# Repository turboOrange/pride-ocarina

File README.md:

# pride-ocarina
An arduino nano based queer electronic ocarina
This was supposed to be used in a pride related workshop where I would spark curiosity with a little electronic soldering course.
The circuit do 2 things. First it has animated leds that shows queer flag colors with animation.
Second it's an electric ocarina based on the 6 holes kind.
It's engineered in a way that it's easy to understand and solder, not to be elegant.
The workshop hasn't been approved so I will keep this unfinished work for maybe a futur pride event.

Here is how it looks like at the moment:

## BOM
- 1 arduino nano
- 6 RGB lets
- 7 push buttons
- 1 9V battery with switch
- 2 double side sticker
- 1 100Ohm resistor
- 6 220Ohm resistor
- 1 motherboard internal speaker
- 1 custom bord
- 1 74HC138
- 1 10kOhm resistor

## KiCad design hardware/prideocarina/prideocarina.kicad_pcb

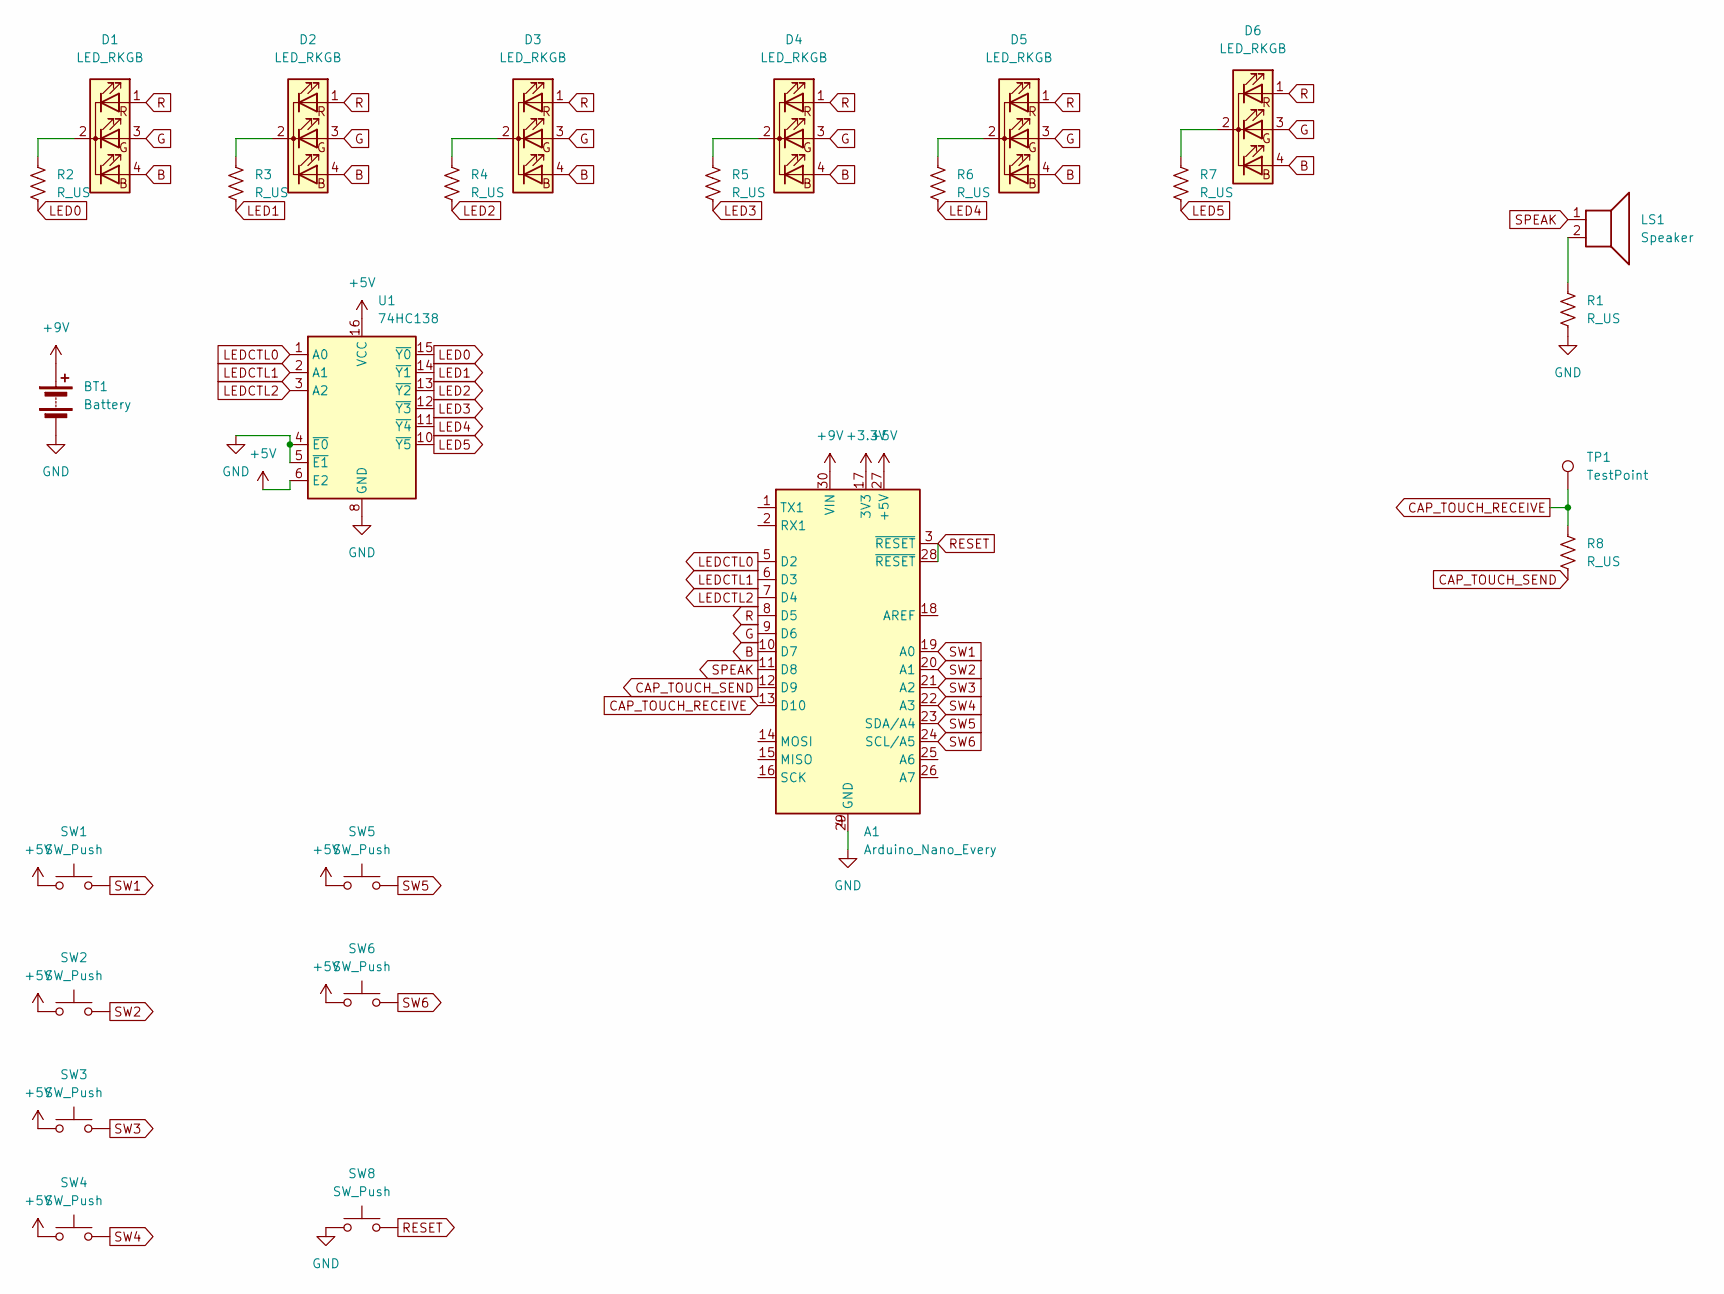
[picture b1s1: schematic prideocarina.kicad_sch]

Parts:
A1: Arduino_Nano_Every; Arduino_Nano
BT1: Battery
D1, D2, D3, D4, D5, D6: LED_RKGB; LED_D5.0mm-4_RGB
LS1: Speaker
R1, R2, R3, R4, R5, R6, R7, R8: R_US; R_Axial_DIN0309_L9.0mm_D3.2mm_P12.70mm_Horizontal
SW1, SW2, SW3, SW4, SW5, SW6, SW8: SW_Push
TP1: TestPoint; MountingHole_8.4mm_M8_Pad_Via
U1: 74HC138; DIP-16_W7.62mm

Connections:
+3.3V: A1.17 (3V3)
+5V: A1.27 (+5V), SW1.1, SW2.1, SW3.1, SW4.1, SW5.1, SW6.1, U1.6 (E2), U1.16 (VCC)
+9V: A1.30 (VIN), BT1.1 (+)
B: A1.10 (D7), D1.4 (BA), D2.4 (BA), D3.4 (BA), D4.4 (BA), D5.4 (BA), D6.4 (BA)
CAP_TOUCH_RECEIVE: A1.13 (D10), R8.1, TP1.1
CAP_TOUCH_SEND: A1.12 (D9), R8.2
G: A1.9 (D6), D1.3 (GA), D2.3 (GA), D3.3 (GA), D4.3 (GA), D5.3 (GA), D6.3 (GA)
GND: A1.4 (GND), A1.29 (GND), BT1.2 (-), R1.2, SW8.1, U1.4 (~E0), U1.5 (~E1), U1.8 (GND)
LED0: R2.2, U1.15 (~Y0)
LED1: R3.2, U1.14 (~Y1)
LED2: R4.2, U1.13 (~Y2)
LED3: R5.2, U1.12 (~Y3)
LED4: R6.2, U1.11 (~Y4)
LED5: R7.2, U1.10 (~Y5)
LEDCTL0: A1.5 (D2), U1.1 (A0)
LEDCTL1: A1.6 (D3), U1.2 (A1)
LEDCTL2: A1.7 (D4), U1.3 (A2)
unnamed: D1.2 (K), R2.1
unnamed: D2.2 (K), R3.1
unnamed: D3.2 (K), R4.1
unnamed: D4.2 (K), R5.1
unnamed: D5.2 (K), R6.1
unnamed: D6.2 (K), R7.1
unnamed: LS1.2, R1.1
R: A1.8 (D5), D1.1 (RA), D2.1 (RA), D3.1 (RA), D4.1 (RA), D5.1 (RA), D6.1 (RA)
RESET: A1.3 (~RESET), A1.28 (~RESET), SW8.2
SPEAK: A1.11 (D8), LS1.1
SW1: A1.19 (A0), SW1.2
SW2: A1.20 (A1), SW2.2
SW3: A1.21 (A2), SW3.2
SW4: A1.22 (A3), SW4.2
SW5: A1.23 (SDA/A4), SW5.2
SW6: A1.24 (SCL/A5), SW6.2

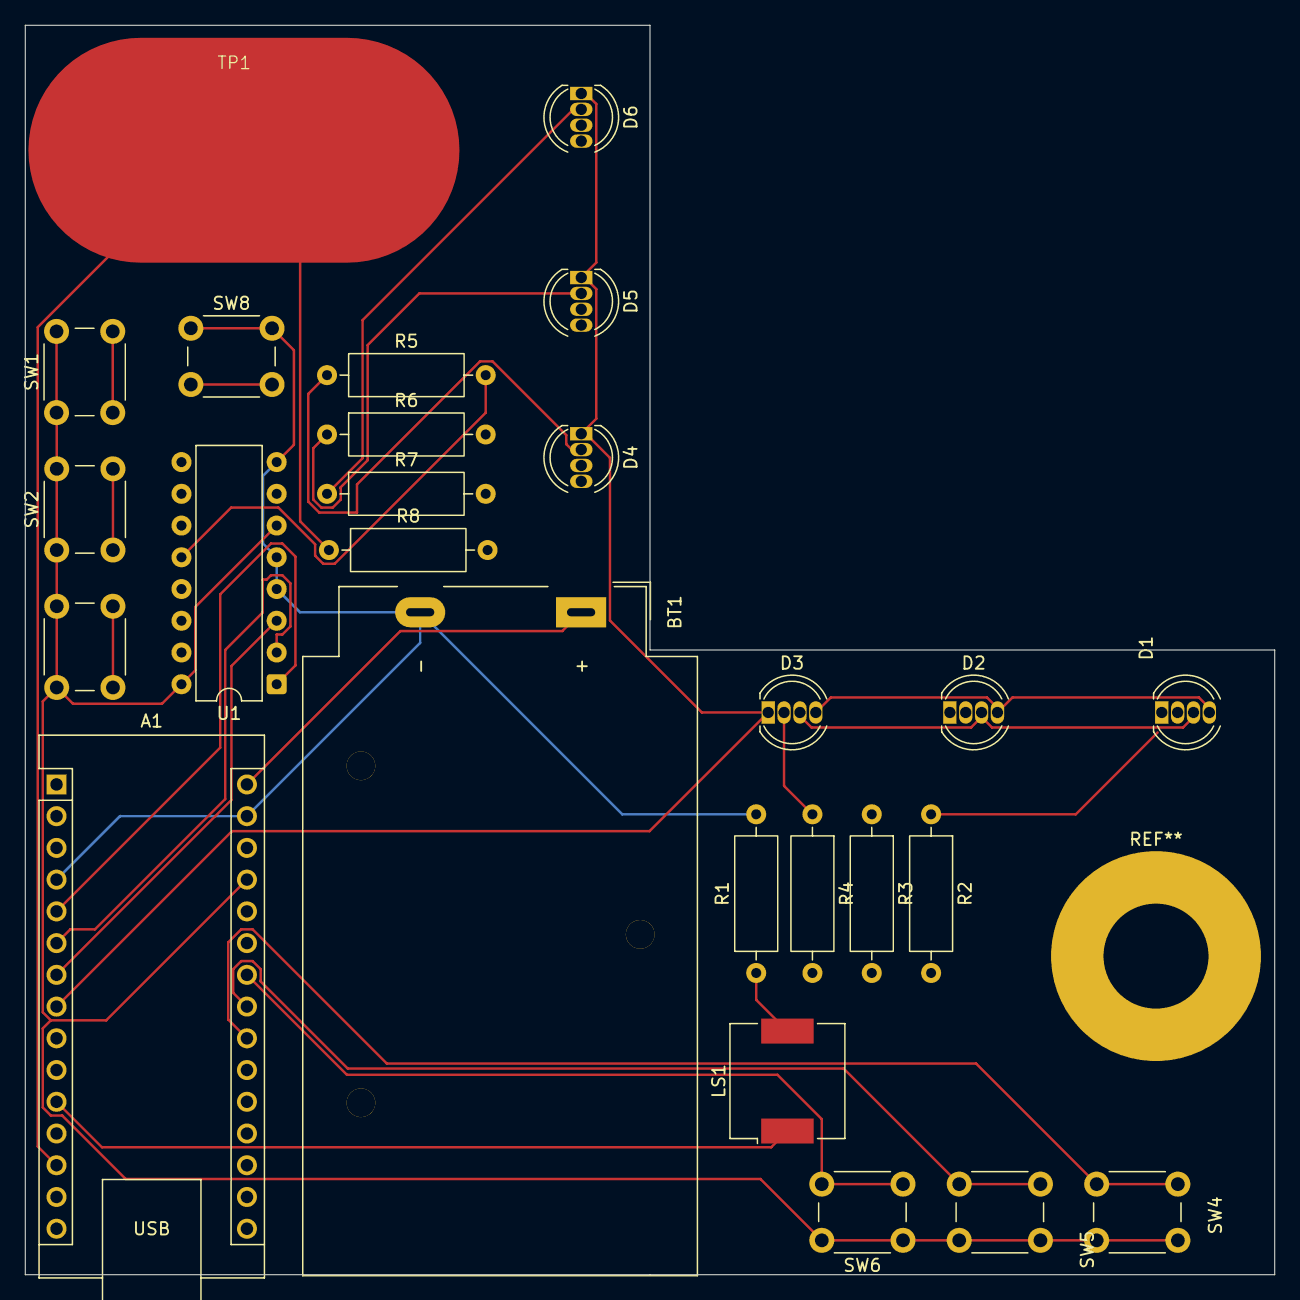
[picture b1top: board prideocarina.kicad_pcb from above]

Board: 2 copper layers, 100.0 x 100.0 mm, 26 parts (0 on the bottom side), 32 nets.

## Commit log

2025-05-29 add bom
2025-05-29 add firmware WORK IN PROGRESS
2025-05-31 start hardware
2025-05-31 update schematics
2025-06-02 finished shema
2025-06-02 removing unessesery files
2025-06-05 finish shema start PCB
2025-06-05 remove backups
2025-06-06 add more description
